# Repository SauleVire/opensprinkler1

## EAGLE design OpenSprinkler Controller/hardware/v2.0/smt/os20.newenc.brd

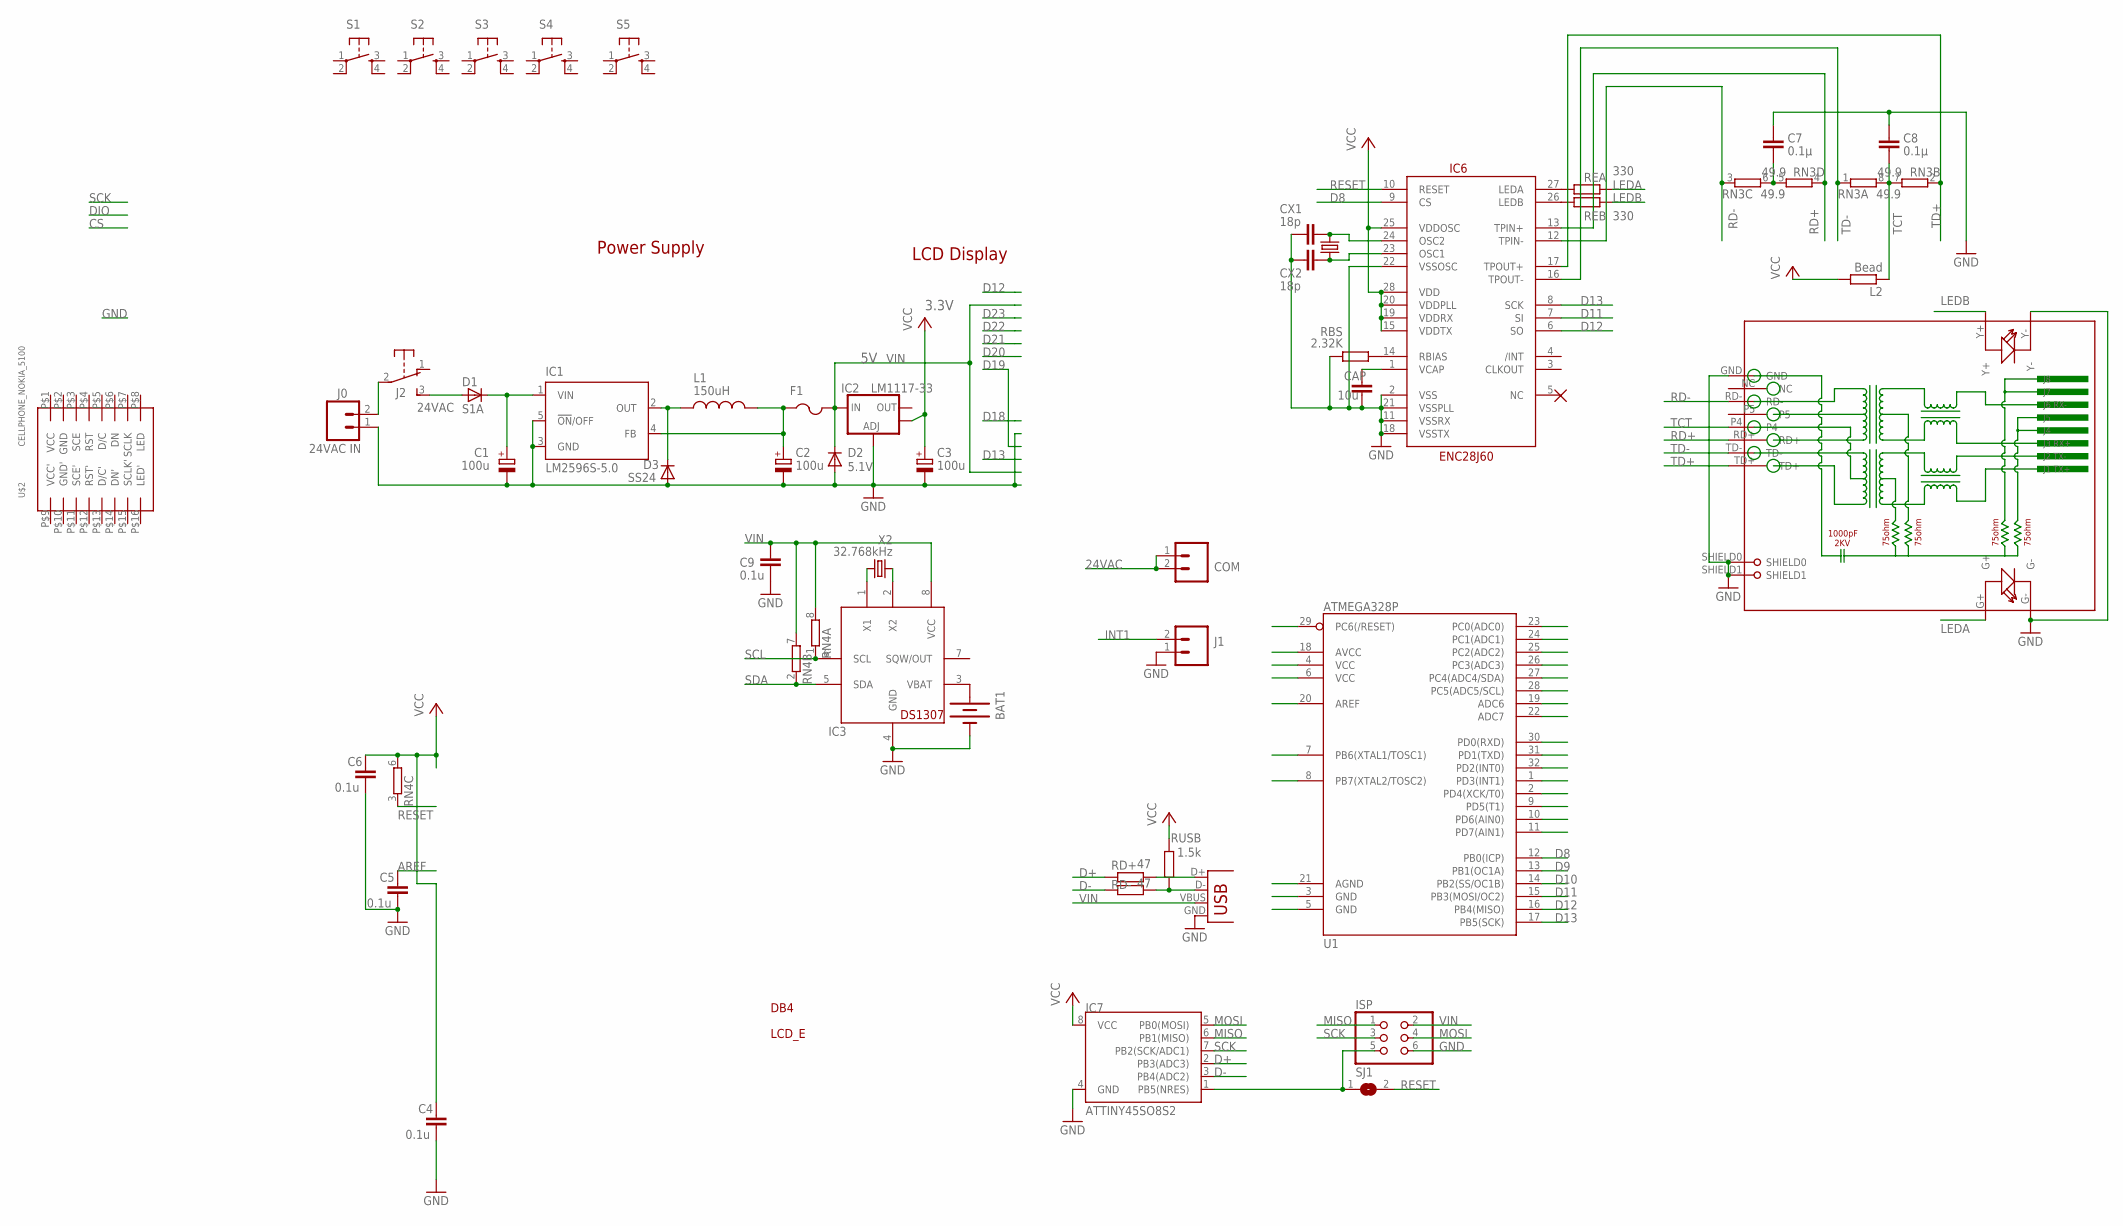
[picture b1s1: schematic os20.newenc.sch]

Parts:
BAT1: BATTERYBATTERY_12MM_SMT; BATTCON_12MM_SMT
C1: 100u; E3,5-8
C2, C3: 100u; PANASONIC_D
C4, C5, C6, C9: 0.1u; C0805
C7, C8: 0.1µ; C0805
CAP: 10u; C0805
COM: M025MM; SCREWTERMINAL-5MM-2
CX1, CX2: 18p; C0805
D1: S1A; DO-214AC
D2: 5.1V; MINIMELF
D3: SS24; DO-214AC
F1: PTCFUSE-1812; 1812
IC1: LM2596S-5.0; TO263-5
IC2: LM1117-33; SOT223
IC3: DS1307; SO08
IC6: ENC28J60; SSOP28DB
IC7: ATTINY45SO8S2; SO8S2
ISP: PINHD-2X3; 2X03
J0: 24VAC IN; SCREWTERMINAL-5MM-2
J1: M025MM; SCREWTERMINAL-5MM-2
J2: EG1206
L1: 150uH; CDRH125
L2: Bead; R0805
RBS: 2.32K; R0805
RD+: 47; R0805
RD-: 47; R0805
REA: 330; R0805
REB: 330; R0805
RJ45: HR911105A
RN3: 49.9; EXB38V
RN4: 4R-NEXB38V; EXB38V
RUSB: 1.5k; R0805
S1, S2, S3, S4, S5: TAC_SWITCHPTH; TACTILE-PTH
SJ1: SJ
U1: ATMEGA328P; TQFP32-08
U$2: CELLPHONE_NOKIA_5100; CELLPHONE_NOKIA_5100_SPARKFUN
USB: USBPTH; USB-B-PTH
X1: 25MHz; HC49US
X2: 32.768kHz; TC26H

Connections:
24VAC: COM.1, COM.2, D1.A, J2.3 (S)
AREF: C5.1
D8: IC6.9 (CS), U1.12 (PB0(ICP))
D9: U1.13 (PB1(OC1A))
D10: U1.14 (PB2(SS/OC1B))
D11: IC6.7 (SI), U1.15 (PB3(MOSI/OC2))
D12: IC6.6 (SO), U1.16 (PB4(MISO))
D13: IC6.8 (SCK), U1.17 (PB5(SCK))
D+: IC7.2 (PB3(ADC3)), RD+.1
D-: IC7.3 (PB4(ADC2)), RD-.1
GND: BAT1.P$1 (-), C1.-, C2.-, C3.-, C4.2, C5.2, C6.2, C7.1, C8.1, C9.2, CAP.2, CX1.2, CX2.2, D2.A, D3.A, IC1.3 (GND), IC1.5 (!ON!/OFF), IC2.1 (ADJ), IC3.4 (GND), IC6.2 (VSS), IC6.11 (VSSRX), IC6.18 (VSSTX), IC6.21 (VSSPLL), IC6.22 (VSSOSC), IC7.4 (GND), ISP.6, J0.1, J1.1, RBS.1, RJ45.G-, RJ45.GND, RJ45.SHIELD0, RJ45.SHIELD1, RJ45.Y-, U$2.P$8 (LED), USB.GND, USB.ID
INT1: J1.2
LEDA: REA.2, RJ45.G+
LEDB: REB.2, RJ45.Y+
MISO: IC7.6 (PB1(MISO)), ISP.1
MOSI: IC7.5 (PB0(MOSI)), ISP.4
unnamed: C1.+, D1.C, IC1.1 (VIN)
unnamed: C2.+, F1.1, IC1.4 (FB), L1.2
unnamed: J0.2, J2.2
unnamed: IC3.1 (X1), X2.2
unnamed: D3.C, IC1.2 (OUT), L1.1
unnamed: IC3.2 (X2), X2.1
unnamed: IC6.27 (LEDA), REA.1
unnamed: BAT1.P$2 (+), IC3.3 (VBAT)
unnamed: IC6.26 (LEDB), REB.1
unnamed: RD+.2, USB.D+
unnamed: CAP.1, IC6.1 (VCAP)
unnamed: CX1.1, IC6.24 (OSC2), X1.2
unnamed: CX2.1, IC6.23 (OSC1), X1.1
unnamed: RD-.2, RUSB.1, USB.D-
unnamed: IC7.1 (PB5(NRES)), ISP.5, SJ1.1
unnamed: C7.2, RN3.5 (2), RN3.6 (2)
unnamed: IC6.14 (RBIAS), RBS.2
RD+: IC6.13 (TPIN+), RJ45.RD+, RN3.4 (1)
RD-: IC6.12 (TPIN-), RJ45.RD-, RN3.3 (1)
RESET: IC6.10 (RESET), RN4.3 (1), SJ1.2
SCK: IC7.7 (PB2(SCK/ADC1)), ISP.3
SCL: IC3.6 (SCL), RN4.1
SDA: IC3.5 (SDA), RN4.2 (1)
TCT: C8.2, L2.1, RJ45.P4, RN3.7 (2), RN3.8 (2)
TD+: IC6.17 (TPOUT+), RJ45.TD+, RN3.2 (1)
TD-: IC6.16 (TPOUT-), RJ45.TD-, RN3.1
V$: U$2.P$1 (VCC)
VCC: C3.+, C4.1, C6.1, IC2.4 (OUT), IC6.15 (VDDTX), IC6.19 (VDDRX), IC6.20 (VDDPLL), IC6.25 (VDDOSC), IC6.28 (VDD), IC7.8 (VCC), L2.2, RN4.6 (2), RUSB.2, U$2.P$6 (DN)
VIN: C9.1, D2.C, F1.2, IC2.3 (IN), IC3.8 (VCC), ISP.2, RN4.7 (2), RN4.8 (2), USB.VBUS

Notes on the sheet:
Power Supply
DB4
LCD Display
3.3V
LCD_E

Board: 2 copper layers, 49 parts (0 on the bottom side), 40 nets, no tracks yet.

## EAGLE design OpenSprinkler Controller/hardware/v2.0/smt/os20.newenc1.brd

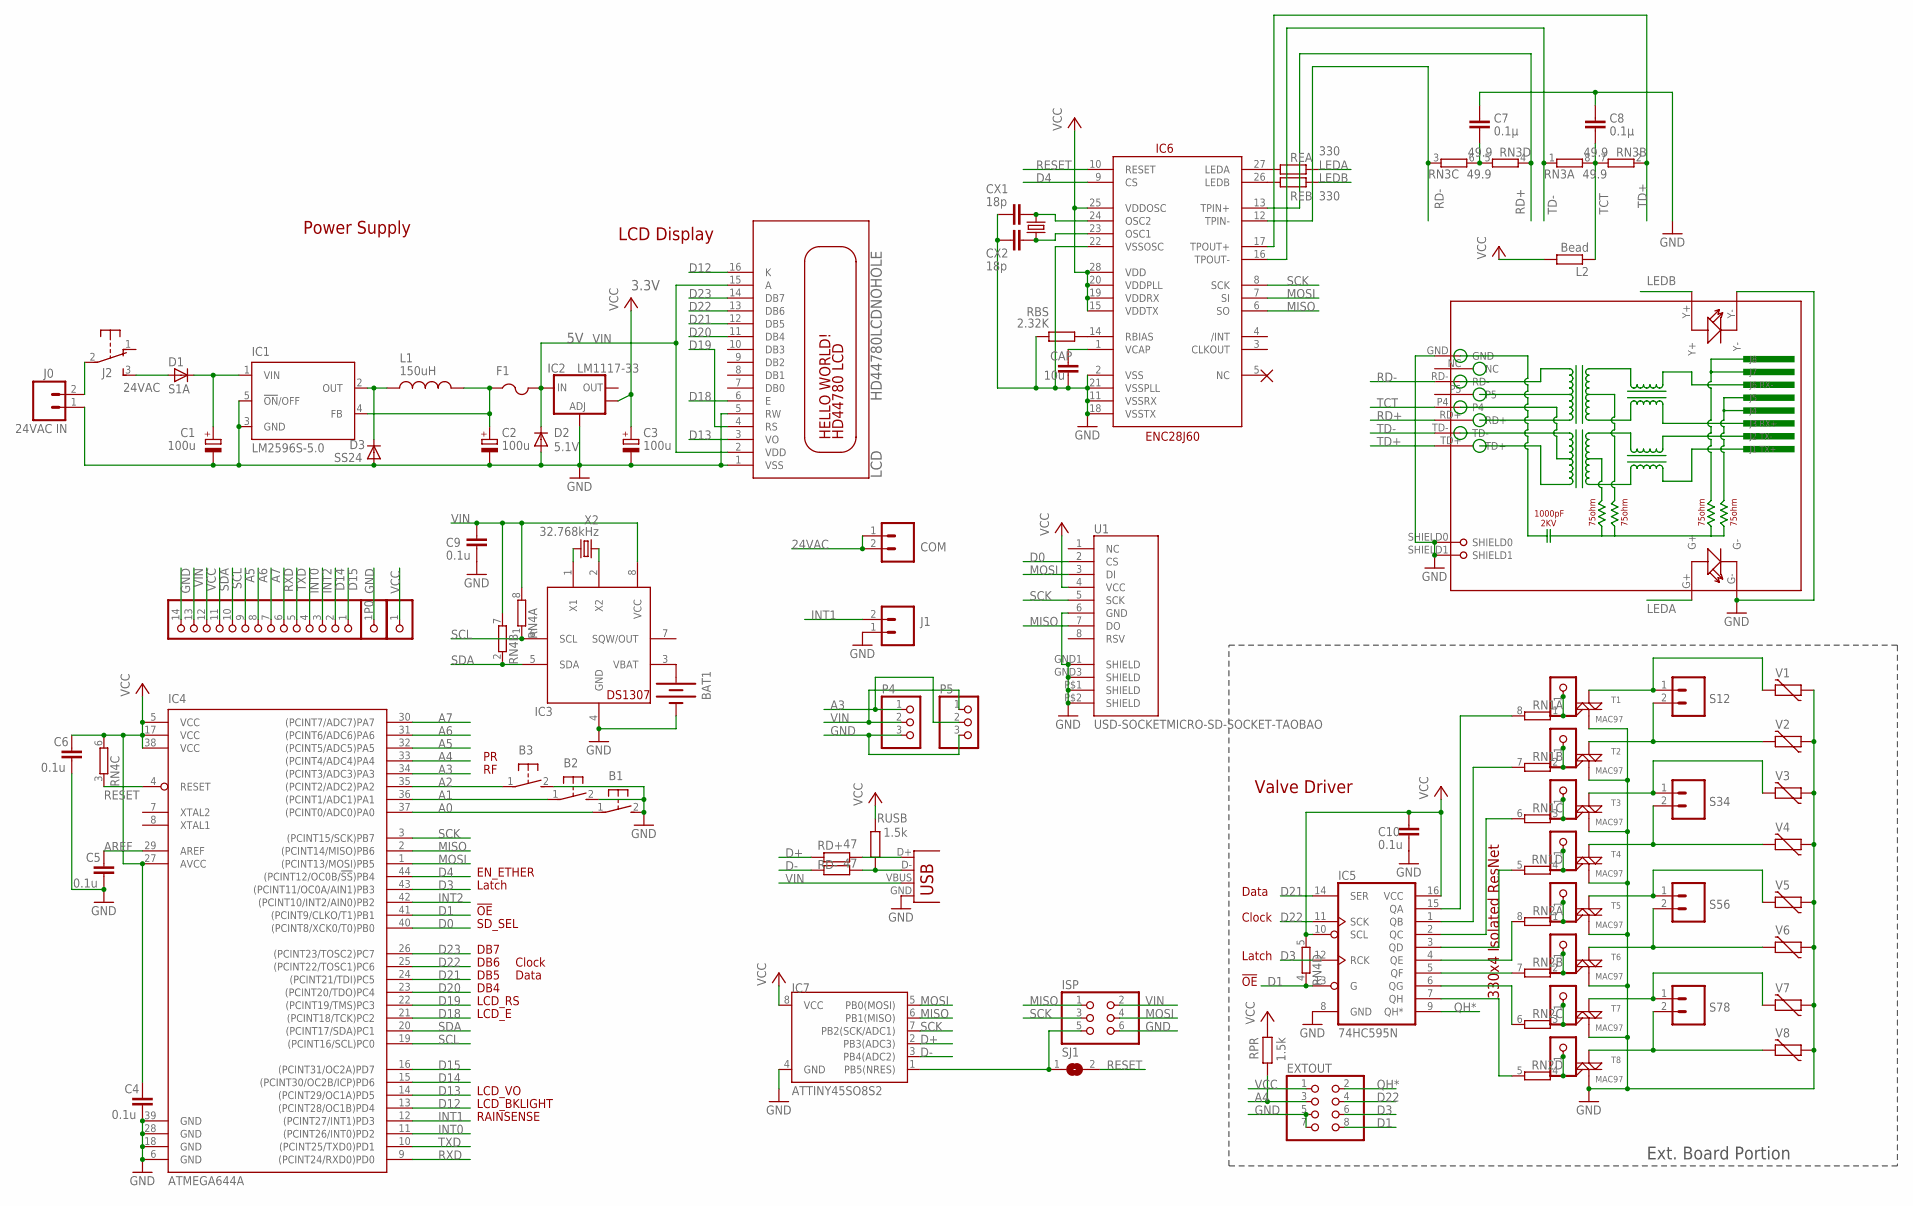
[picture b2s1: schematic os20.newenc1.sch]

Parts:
B1, B2, B3: 31-XX; B3F-31XX
BAT1: BATTERYBATTERY_12MM_SMT; BATTCON_12MM_SMT
C1: 100u; E3,5-8
C2, C3: 100u; PANASONIC_D
C4, C5, C6, C9, C10: 0.1u; C0805
C7, C8: 0.1µ; C0805
CAP: 10u; C0805
COM: M025MM; SCREWTERMINAL-5MM-2
CX1, CX2: 18p; C0805
D1: S1A; DO-214AC
D2: 5.1V; MINIMELF
D3: SS24; DO-214AC
EXTOUT: PINHD-2X4; 2X04
F1: PTCFUSE-1812; 1812
IC1: LM2596S-5.0; TO263-5
IC2: LM1117-33; SOT223
IC3: DS1307; SO08
IC4: ATMEGA644A; TQFP44
IC5: 74HC595N; SO16
IC6: ENC28J60; SOIC28WLONG
IC7: ATTINY45SO8S2; SO8S2
ISP: PINHD-2X3; 2X03
J0: 24VAC IN; SCREWTERMINAL-5MM-2
J1: M025MM; SCREWTERMINAL-5MM-2
J2: EG1206
JP2, JP3, JP4, JP5, JP6, JP7, JP8, JP9: PINHD-1X1CB; 1X01-CLEANBIG
L1: 150uH; CDRH125
L2: Bead; R0805
LCD: HD44780LCDNOHOLE; LCD1602A
P0: PINHD-1X14-CB; 1X14-CB
P1, P2: PINHD-1X1CB; 1X01-CLEANBIG
P4, P5: PINHD-1X3; 1X03
RBS: 2.32K; R0805
RD+: 47; R0805
RD-: 47; R0805
REA: 330; R0805
REB: 330; R0805
RJ45: HR911105A
RN1, RN2, RN4: 4R-NEXB38V; EXB38V
RN3: 49.9; EXB38V
RPR: 1.5k; R0805
RUSB: 1.5k; R0805
S12, S34, S56, S78: M025MM; SCREWTERMINAL-5MM-2
SJ1: SJ
T1, T2, T3, T4, T5, T6, T7, T8: MAC97; SOT223
U1: USD-SOCKETMICRO-SD-SOCKET-TAOBAO; MICRO-SD-SOCKET-TAOBAO
USB: USBPTH; USB-B-PTH
V1, V2, V3, V4, V5, V6, V7, V8: MOV; R-5
X1: 25MHz; HC49US
X2: 32.768kHz; TC26H

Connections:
24VAC: COM.1, COM.2, D1.A, J2.3 (S)
A0: B1.1, IC4.37 ((PCINT0/ADC0)PA0)
A1: B2.1, IC4.36 ((PCINT1/ADC1)PA1)
A2: B3.1, IC4.35 ((PCINT2/ADC2)PA2)
A3: IC4.34 ((PCINT3/ADC3)PA3), P4.1, P5.2
A4: EXTOUT.3, IC4.33 ((PCINT4/ADC4)PA4), RPR.1
A5: IC4.32 ((PCINT5/ADC5)PA5), P0.9
A6: IC4.31 ((PCINT6/ADC6)PA6), P0.8
A7: IC4.30 ((PCINT7/ADC7)PA7), P0.7
AREF: C5.1, IC4.29 (AREF)
D0: IC4.40 ((PCINT8/XCK0/T0)PB0), U1.2 (CS)
D1: EXTOUT.8, IC4.41 ((PCINT9/CLKO/T1)PB1), IC5.13 (G), RN4.4 (1)
D3: EXTOUT.6, IC4.43 ((PCINT11/OC0A/AIN1)PB3), IC5.12 (RCK)
D4: IC4.44 ((PCINT12/OC0B/!SS!)PB4), IC6.9 (CS)
D12: IC4.13 ((PCINT28/OC1B)PD4), LCD.16 (K)
D13: IC4.14 ((PCINT29/OC1A)PD5), LCD.3 (VO)
D14: IC4.15 ((PCINT30/OC2B/ICP)PD6), P0.2
D15: IC4.16 ((PCINT31/OC2A)PD7), P0.1
D18: IC4.21 ((PCINT18/TCK)PC2), LCD.6 (E)
D19: IC4.22 ((PCINT19/TMS)PC3), LCD.4 (RS)
D20: IC4.23 ((PCINT20/TDO)PC4), LCD.11 (DB4)
D21: IC4.24 ((PCINT21/TDI)PC5), IC5.14 (SER), LCD.12 (DB5)
D22: EXTOUT.4, IC4.25 ((PCINT22/TOSC1)PC6), IC5.11 (SCK), LCD.13 (DB6)
D23: IC4.26 ((PCINT23/TOSC2)PC7), LCD.14 (DB7)
D+: IC7.2 (PB3(ADC3)), RD+.1
D-: IC7.3 (PB4(ADC2)), RD-.1
GND: B1.2 (S), B2.2 (S), B3.2 (S), BAT1.P$1 (-), C1.-, C2.-, C3.-, C4.2, C5.2, C6.2, C7.1, C8.1, C9.2, C10.2, CAP.2, CX1.2, CX2.2, D2.A, D3.A, EXTOUT.5, EXTOUT.7, IC1.3 (GND), IC1.5 (!ON!/OFF), IC2.1 (ADJ), IC3.4 (GND), IC4.6 (GND), IC4.18 (GND), IC4.28 (GND), IC4.39 (GND), IC5.8 (GND), IC6.2 (VSS), IC6.11 (VSSRX), IC6.18 (VSSTX), IC6.21 (VSSPLL), IC6.22 (VSSOSC), IC7.4 (GND), ISP.6, J0.1, J1.1, LCD.1 (VSS), LCD.5 (RW), P0.14, P1.1, P4.3, P5.3, RBS.1, RJ45.G-, RJ45.GND, RJ45.SHIELD0, RJ45.SHIELD1, RJ45.Y-, T1.1 (M1), T2.1 (M1), T3.1 (M1), T4.1 (M1), T5.1 (M1), T6.1 (M1), T7.1 (M1), T8.1 (M1), U1.6 (GND), U1.GND1 (SHIELD), U1.GND3 (SHIELD), U1.P$1 (SHIELD), U1.P$2 (SHIELD), USB.GND, V1.1, V2.1, V3.1, V4.1, V5.1, V6.1, V7.1, V8.1
INT0: IC4.11 ((PCINT26/INT0)PD2), P0.4
INT1: IC4.12 ((PCINT27/INT1)PD3), J1.2
INT2: IC4.42 ((PCINT10/INT2/AIN0)PB2), P0.3
LEDA: REA.2, RJ45.G+
LEDB: REB.2, RJ45.Y+
MISO: IC4.2 ((PCINT14/MISO)PB6), IC6.6 (SO), IC7.6 (PB1(MISO)), ISP.1, U1.7 (DO)
MOSI: IC4.1 ((PCINT13/MOSI)PB5), IC6.7 (SI), IC7.5 (PB0(MOSI)), ISP.4, U1.3 (DI)
unnamed: C1.+, D1.C, IC1.1 (VIN)
unnamed: C2.+, F1.1, IC1.4 (FB), L1.2
unnamed: JP2.1, RN1.1, T1.3 (G)
unnamed: IC5.5 (QF), RN2.7 (2)
unnamed: IC5.6 (QG), RN2.6 (2)
unnamed: J0.2, J2.2
unnamed: IC5.7 (QH), RN2.5 (2)
unnamed: IC3.1 (X1), X2.2
unnamed: D3.C, IC1.2 (OUT), L1.1
unnamed: IC5.4 (QE), RN2.8 (2)
unnamed: IC5.3 (QD), RN1.5 (2)
unnamed: IC5.2 (QC), RN1.6 (2)
unnamed: IC5.1 (QB), RN1.7 (2)
unnamed: IC5.15 (QA), RN1.8 (2)
unnamed: JP3.1, RN1.2 (1), T2.3 (G)
unnamed: S12.1, T1.4 (M2), V1.2
unnamed: S12.2, T2.4 (M2), V2.2
unnamed: S34.1, T3.4 (M2), V3.2
unnamed: JP4.1, RN1.3 (1), T3.3 (G)
unnamed: S34.2, T4.4 (M2), V4.2
unnamed: JP5.1, RN1.4 (1), T4.3 (G)
unnamed: S56.1, T5.4 (M2), V5.2
unnamed: S56.2, T6.4 (M2), V6.2
unnamed: S78.1, T7.4 (M2), V7.2
unnamed: S78.2, T8.4 (M2), V8.2
unnamed: JP6.1, RN2.1, T5.3 (G)
unnamed: JP7.1, RN2.2 (1), T6.3 (G)
unnamed: JP8.1, RN2.3 (1), T7.3 (G)
unnamed: JP9.1, RN2.4 (1), T8.3 (G)
unnamed: IC3.2 (X2), X2.1
unnamed: IC6.27 (LEDA), REA.1
unnamed: BAT1.P$2 (+), IC3.3 (VBAT)
unnamed: IC6.26 (LEDB), REB.1
unnamed: RD+.2, USB.D+
unnamed: CAP.1, IC6.1 (VCAP)
unnamed: CX1.1, IC6.24 (OSC2), X1.2
unnamed: CX2.1, IC6.23 (OSC1), X1.1
unnamed: RD-.2, RUSB.1, USB.D-
unnamed: IC7.1 (PB5(NRES)), ISP.5, SJ1.1
unnamed: C7.2, RN3.5 (2), RN3.6 (2)
unnamed: IC6.14 (RBIAS), RBS.2
QH*: EXTOUT.2, IC5.9 (QH*)
RD+: IC6.13 (TPIN+), RJ45.RD+, RN3.4 (1)
RD-: IC6.12 (TPIN-), RJ45.RD-, RN3.3 (1)
RESET: IC4.4 (RESET), IC6.10 (RESET), RN4.3 (1), SJ1.2
RXD: IC4.9 ((PCINT24/RXD0)PD0), P0.6
SCK: IC4.3 ((PCINT15/SCK)PB7), IC6.8 (SCK), IC7.7 (PB2(SCK/ADC1)), ISP.3, U1.5 (SCK)
SCL: IC3.6 (SCL), IC4.19 ((PCINT16/SCL)PC0), P0.10, RN4.1
SDA: IC3.5 (SDA), IC4.20 ((PCINT17/SDA)PC1), P0.11, RN4.2 (1)
TCT: C8.2, L2.1, RJ45.P4, RN3.7 (2), RN3.8 (2)
TD+: IC6.17 (TPOUT+), RJ45.TD+, RN3.2 (1)
TD-: IC6.16 (TPOUT-), RJ45.TD-, RN3.1
TXD: IC4.10 ((PCINT25/TXD0)PD1), P0.5
VCC: C3.+, C4.1, C6.1, C10.1, EXTOUT.1, IC2.4 (OUT), IC4.5 (VCC), IC4.17 (VCC), IC4.27 (AVCC), IC4.38 (VCC), IC5.10 (SCL), IC5.16 (VCC), IC6.15 (VDDTX), IC6.19 (VDDRX), IC6.20 (VDDPLL), IC6.25 (VDDOSC), IC6.28 (VDD), IC7.8 (VCC), L2.2, P0.12, P2.1, RN4.5 (2), RN4.6 (2), RPR.2, RUSB.2, U1.4 (VCC)
VIN: C9.1, D2.C, F1.2, IC2.3 (IN), IC3.8 (VCC), ISP.2, LCD.2 (VDD), LCD.15 (A), P0.13, P4.2, P5.1, RN4.7 (2), RN4.8 (2), USB.VBUS

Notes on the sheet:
Power Supply
Valve Driver
Data
Clock
Latch
DB4
330x4 Isolated ResNet
LCD Display
EN_ETHER
3.3V
DB7
LCD_E
LCD_RS
DB6
DB5
Ext. Board Portion
!OE
RAINSENSE
LCD_BKLIGHT
LCD_VO
SD_SEL

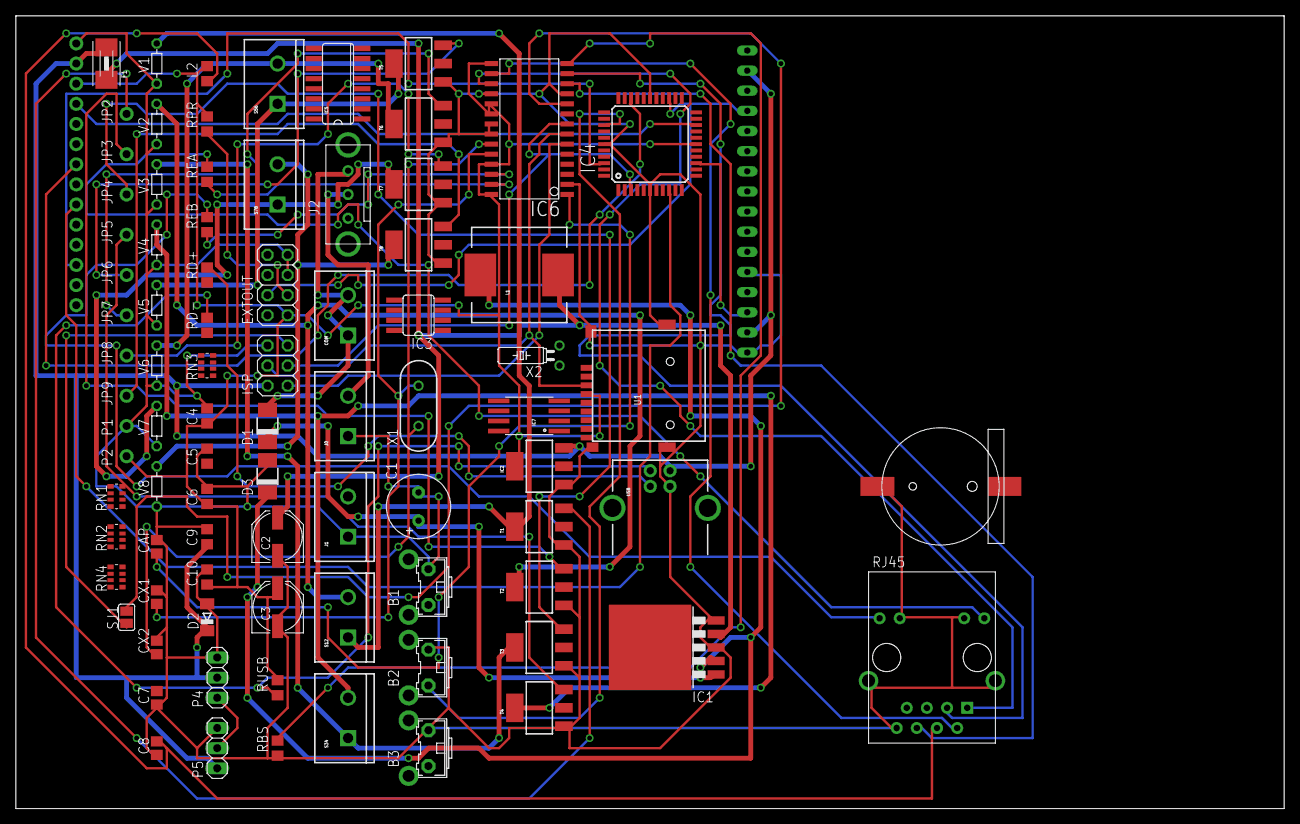
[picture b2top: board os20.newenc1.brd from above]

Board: 2 copper layers, 160.0 x 100.0 mm, 87 parts (0 on the bottom side), 89 nets.

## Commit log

2014-01-13 pradžia
2014-01-13 pakeistas lcd i nokia
2014-01-23 smulkmenos..
2014-01-30 Pakeista Nokia LCD biblioteka
2014-01-31 pirmyn...

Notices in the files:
parts and their libraries:
SparkFun-DigitalIC: Licensing: CC v3.0 Share-Alike You are welcome to use this library for commercial purposes.
